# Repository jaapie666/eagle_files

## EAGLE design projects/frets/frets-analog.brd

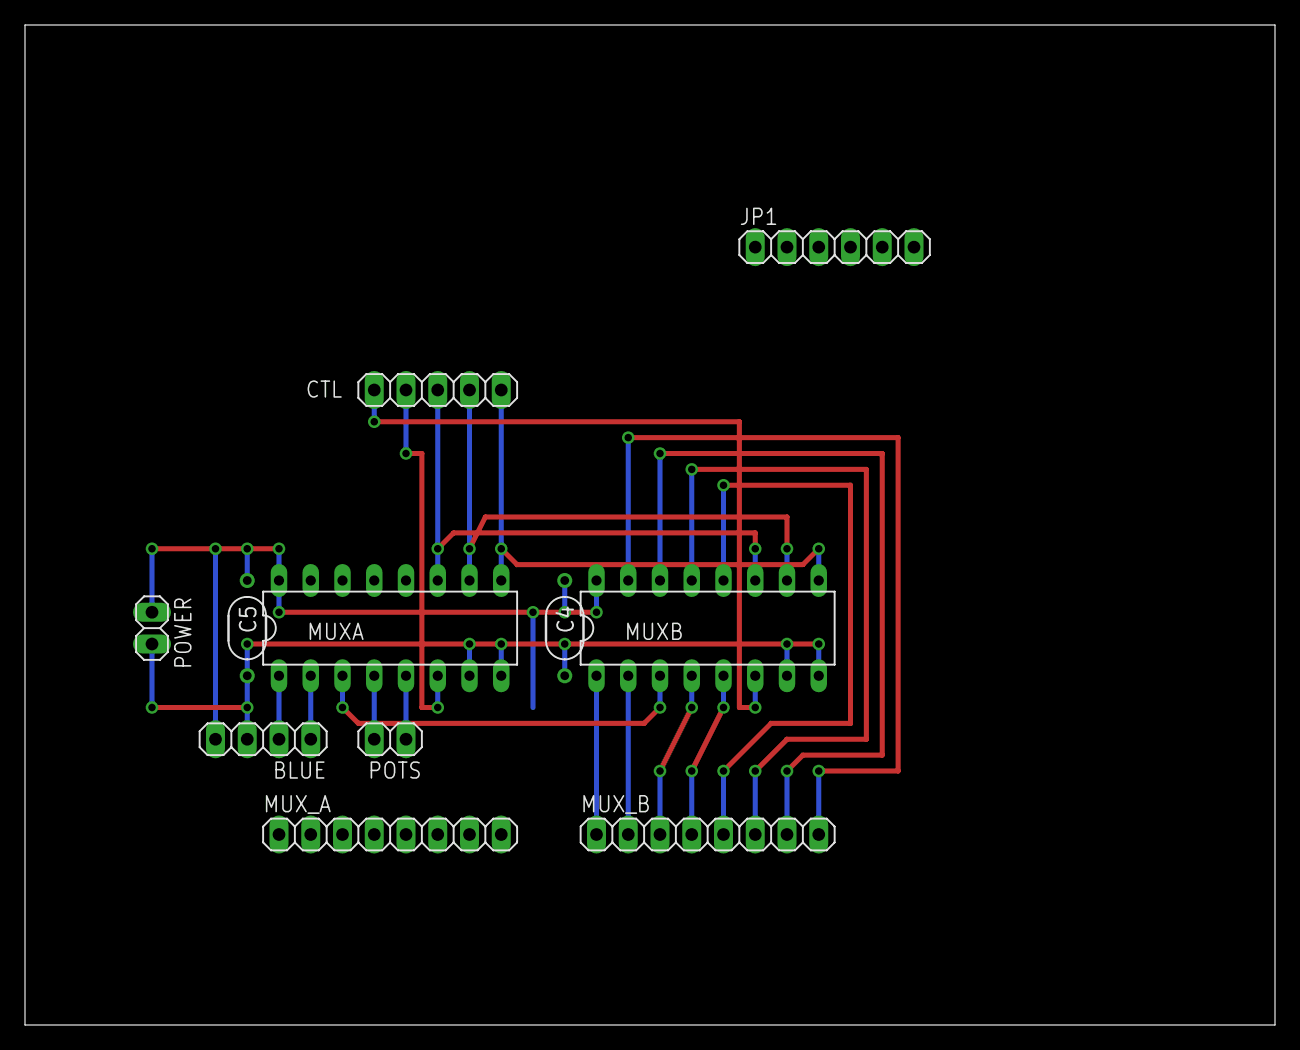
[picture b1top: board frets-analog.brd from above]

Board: 2 copper layers, 100.0 x 80.0 mm, 11 parts (0 on the bottom side), 20 nets.

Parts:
BLUE: 1X04
C4, C5: 100n; 050X030_050_3
CTL: 1X05
JP1: 1X06
MUXA: 4051N; DIL16
MUXB: 4051N; DIL16
MUX_A: 1X08
MUX_B: 1X08
POTS: 1X02
POWER: 1X02

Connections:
GND: BLUE.3, C4.2, C5.2, MUXA.7, MUXA.8, MUXB.7, MUXB.8, POWER.2
INH_A: CTL.4, MUXA.6
INH_B: CTL.5, MUXB.6
JOY_X: BLUE.1, MUXA.2
JOY_Y: BLUE.2, MUXA.1
MX_A: CTL.3, MUXA.11, MUXB.11
MX_B: CTL.2, MUXA.10, MUXB.10
MX_C: CTL.1, MUXA.9, MUXB.9
unnamed: JP1.1, MUXA.3, MUXB.3
unnamed: MUXB.1, MUX_B.1
unnamed: MUXB.2, MUX_B.2
unnamed: MUXB.4, MUX_B.3
unnamed: MUXB.5, MUX_B.4
unnamed: MUXB.12, MUX_B.5
unnamed: MUXB.13, MUX_B.6
unnamed: MUXB.14, MUX_B.7
unnamed: MUXB.15, MUX_B.8
POT_A: MUXA.5, POTS.1
POT_B: MUXA.4, POTS.2
VA: BLUE.4, C4.1, C5.1, MUXA.16, MUXB.16, POWER.1

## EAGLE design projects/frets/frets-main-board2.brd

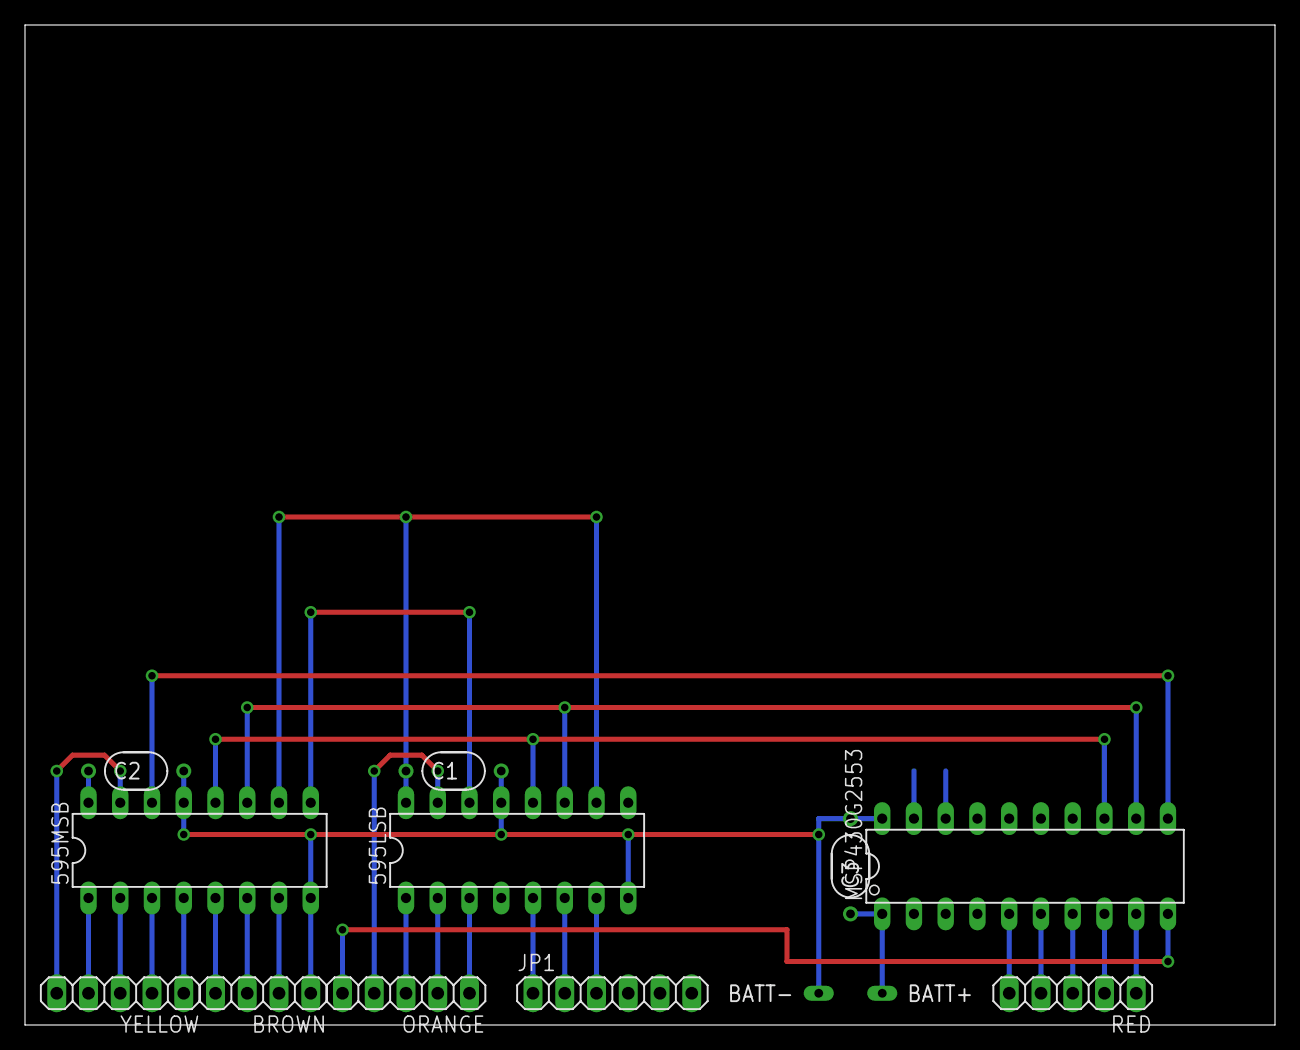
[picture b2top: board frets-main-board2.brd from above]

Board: 2 copper layers, 100.0 x 80.0 mm, 13 parts (0 on the bottom side), 30 nets.

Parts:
595LSB, 595MSB: 74LS595N; DIL16
BATT+: LONG
BATT-: LONG
BROWN: 1X04
C1, C2, C3: 100n; 050X030_050_3
JP1: 1X06
MSP430G2553: G2XX3---N20; N20
ORANGE: 1X05
RED: 1X05
YELLOW: 1X05

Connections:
A_IN: JP1.6, MSP430G2553.2
D0: MSP430G2553.5, RED.5
D1: MSP430G2553.6, RED.4
D2: MSP430G2553.7, RED.3
D3: MSP430G2553.8, RED.2
D4: MSP430G2553.9, RED.1
D5: MSP430G2553.10, ORANGE.5
GND: 595LSB.8, 595LSB.13, 595MSB.8, 595MSB.13, BATT-.1, BROWN.1, C1.2, C2.2, C3.2, MSP430G2553.20
INH_A: JP1.4, MSP430G2553.18
INH_B: JP1.5, MSP430G2553.19
MX_A: 595LSB.5, JP1.1
MX_B: 595LSB.6, JP1.2
MX_C: 595LSB.7, JP1.3
unnamed: 595LSB.14, 595MSB.9
RCK: 595LSB.12, 595MSB.12, MSP430G2553.13
SCK: 595LSB.11, 595MSB.11, MSP430G2553.12
SER: 595MSB.14, MSP430G2553.11
SR4: 595LSB.3, ORANGE.1
SR5: 595LSB.2, ORANGE.2
SR6: 595LSB.1, ORANGE.3
SR7: 595LSB.15, ORANGE.4
SR8: 595MSB.7, BROWN.2
SR9: 595MSB.6, BROWN.3
SR10: 595MSB.5, BROWN.4
SR11: 595MSB.4, YELLOW.1
SR12: 595MSB.3, YELLOW.2
SR13: 595MSB.2, YELLOW.3
SR14: 595MSB.1, YELLOW.4
SR15: 595MSB.15, YELLOW.5
VA: 595LSB.10, 595LSB.16, 595MSB.10, 595MSB.16, BATT+.1, C1.1, C2.1, C3.1, MSP430G2553.1

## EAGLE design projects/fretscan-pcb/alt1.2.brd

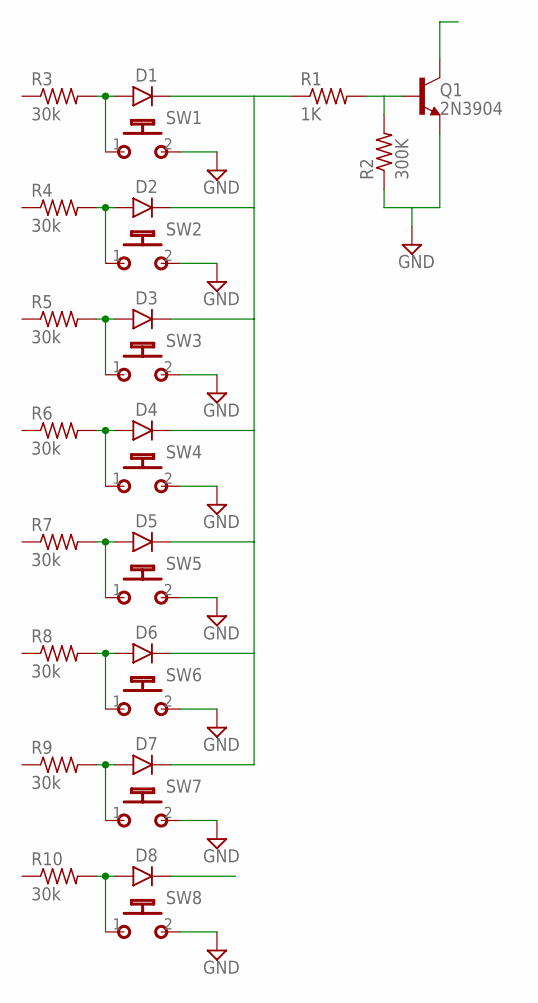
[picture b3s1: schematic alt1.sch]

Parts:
D1, D2, D3, D4, D5, D6, D7, D8: 1N4148-3; DO35-3
Q1: 2N3904; TO92-
R1: 1K; R0207/3
R2: 300K; R0207/3
R3, R4, R5, R6, R7, R8, R9, R10: 30k; R0207/3
SW1, SW2, SW3, SW4, SW5, SW6, SW7, SW8: MOMENTARYSPST1; SPST

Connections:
GND: Q1.3 (E), R2.1, SW1.2 (S), SW2.2 (S), SW3.2 (S), SW4.2 (S), SW5.2 (S), SW6.2 (S), SW7.2 (S), SW8.2 (S)
unnamed: Q1.2 (B), R1.2, R2.2
unnamed: D2.A, R4.2, SW2.1
unnamed: D1.A, R3.2, SW1.1
unnamed: D3.A, R5.2, SW3.1
unnamed: D4.A, R6.2, SW4.1
unnamed: D5.A, R7.2, SW5.1
unnamed: D6.A, R8.2, SW6.1
unnamed: D1.C, D2.C, D3.C, D4.C, D5.C, D6.C, D7.C, R1.1
unnamed: D7.A, R9.2, SW7.1
unnamed: D8.A, R10.2, SW8.1

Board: 2 copper layers, 27 parts (0 on the bottom side), 11 nets, no tracks yet.

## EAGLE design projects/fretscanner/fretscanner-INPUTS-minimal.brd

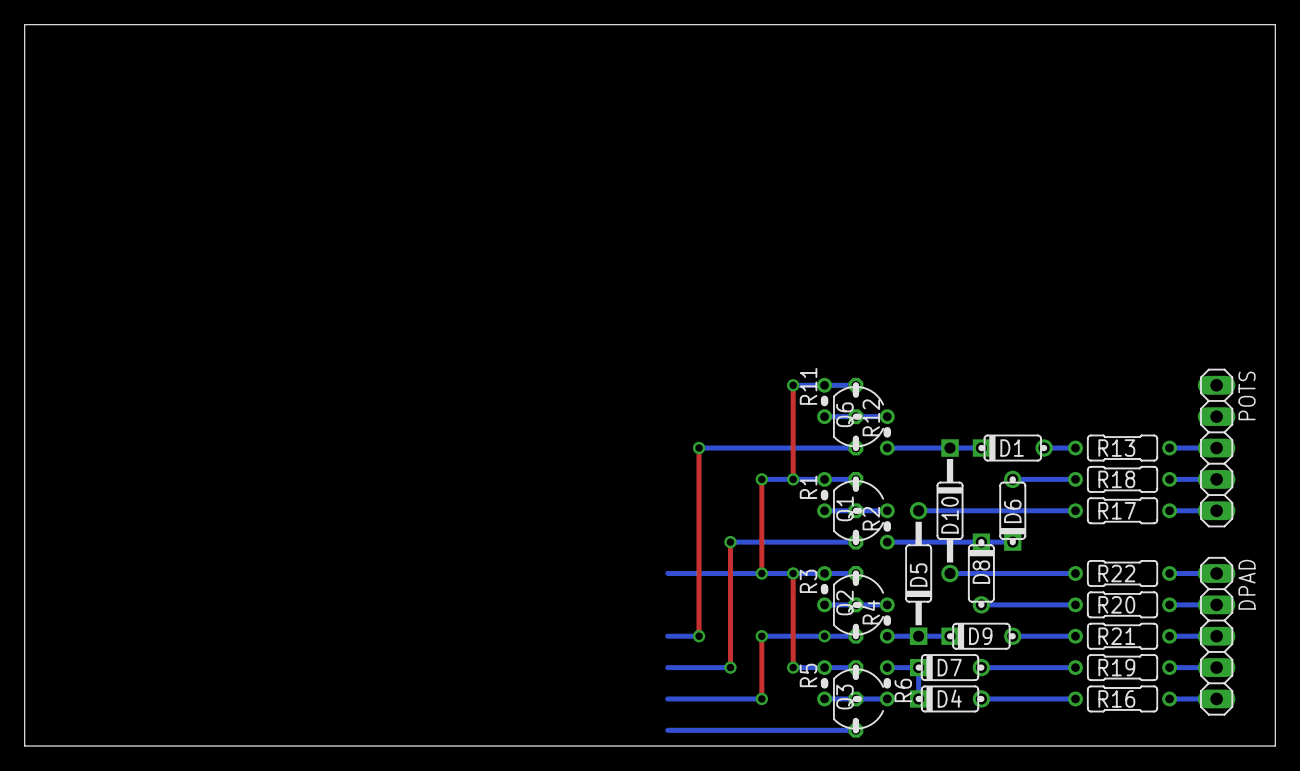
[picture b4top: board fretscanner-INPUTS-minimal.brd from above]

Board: 2 copper layers, 101.3 x 58.4 mm, 30 parts (0 on the bottom side), 25 nets.

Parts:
D1, D4, D6, D7, D8, D9: 1N4148-2; DO35-2
D5, D10: 1N4148-4; DO35-4
DPAD: 1X05
POTS: 1X05
Q1, Q2, Q3, Q6: 2N3904; TO92-
R1, R3, R5, R11: 300k; R0207/1V
R2, R4, R6, R12: 1k; R0207/1V
R13, R16, R17, R18, R19, R20, R21, R22: 30k; R0207/3

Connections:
BACK: POTS.4, R18.1
D_DOWN: DPAD.1, R22.1
D_LEFT: DPAD.2, R20.1
D_RIGHT: DPAD.3, R21.1
D_UP: DPAD.4, R19.1
GND: Q1.3, Q2.3, Q3.3, Q6.3, R1.2, R3.2, R5.2, R11.2
unnamed: Q2.2, R3.1, R4.2
unnamed: D5.C, D9.C, R4.1
unnamed: Q3.2, R5.1, R6.2
unnamed: Q1.2, R1.1, R2.2
unnamed: D6.C, D8.C, R2.1
unnamed: D4.A, R16.2
unnamed: D5.A, R17.2
unnamed: D4.C, D7.C, R6.1
unnamed: D6.A, R18.2
unnamed: D1.A, R13.2
unnamed: Q6.2, R11.1, R12.2
unnamed: D1.C, D10.C, R12.1
unnamed: D7.A, R19.2
unnamed: D8.A, R20.2
unnamed: D9.A, R21.2
unnamed: D10.A, R22.2
SIDE_B: POTS.5, R17.1
START: POTS.3, R13.1
X_BUTTON: DPAD.5, R16.1

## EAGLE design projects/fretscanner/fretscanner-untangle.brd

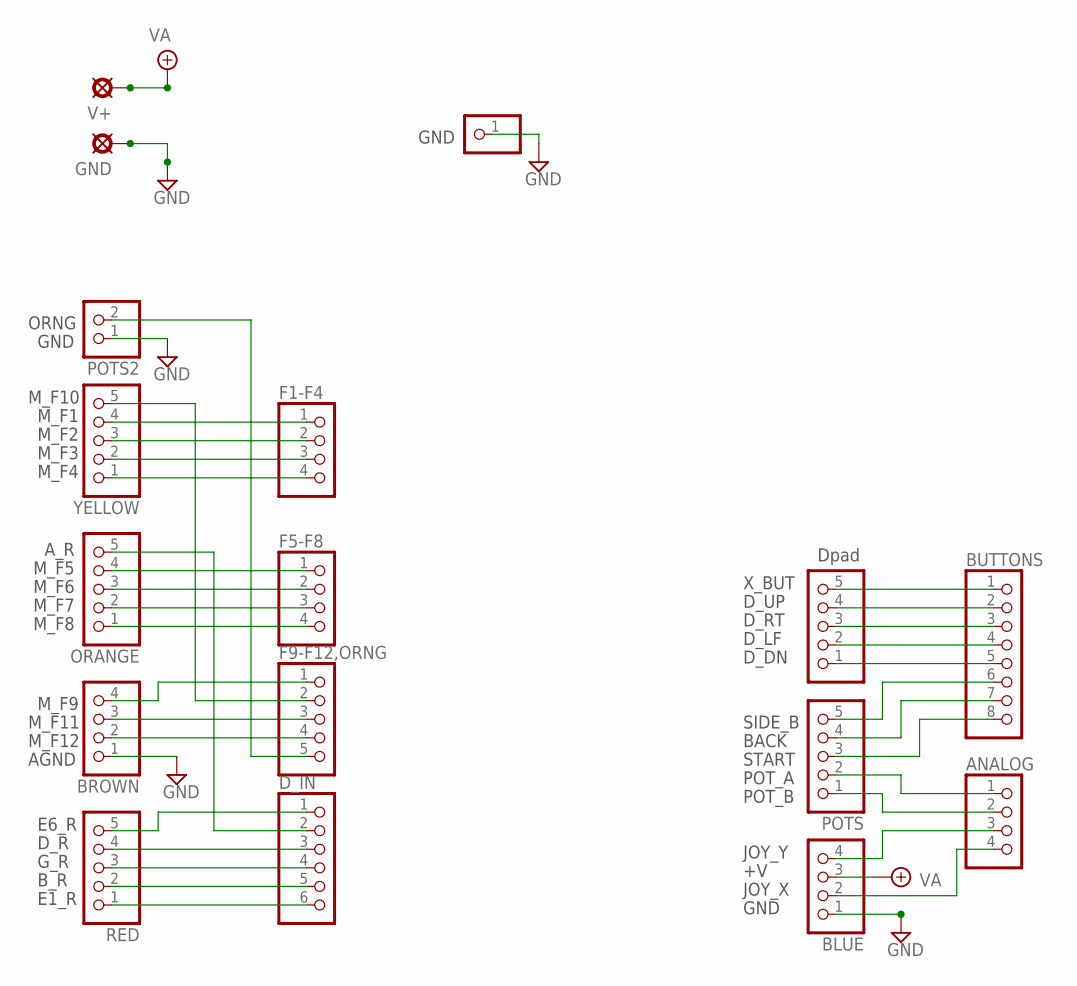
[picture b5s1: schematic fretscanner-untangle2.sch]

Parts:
ANALOG: PINHD-1X4; 1X04
BLUE: PINHD-1X4; 1X04
BROWN: PINHD-1X4; 1X04
BUTTONS: PINHD-1X8; 1X08
DPAD: PINHD-1X5; 1X05
DPAD2: PINHD-1X1; 1X01
D_IN: PINHD-1X6; 1X06
F1-F4, F5-F8: PINHD-1X4; 1X04
F9-F12,ORNG: PINHD-1X5; 1X05
GND: PADL; LONG
ORANGE: PINHD-1X5; 1X05
POTS: PINHD-1X5; 1X05
POTS2: PINHD-1X2; 1X02
RED: PINHD-1X5; 1X05
V+: PADL; LONG
YELLOW: PINHD-1X5; 1X05

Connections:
BACK: BUTTONS.7, POTS.4
D0: D_IN.1, RED.5
GND: BLUE.1, BROWN.1, DPAD2.1, GND.1, POTS2.1
JOY_X: ANALOG.4, BLUE.2
JOY_Y: ANALOG.3, BLUE.4
unnamed: F1-F4.1, YELLOW.4
unnamed: F1-F4.2, YELLOW.3
unnamed: F1-F4.3, YELLOW.2
unnamed: F1-F4.4, YELLOW.1
unnamed: F5-F8.1, ORANGE.4
unnamed: F5-F8.2, ORANGE.3
unnamed: F5-F8.3, ORANGE.2
unnamed: F5-F8.4, ORANGE.1
unnamed: BROWN.4, F9-F12,ORNG.1
unnamed: F9-F12,ORNG.2, YELLOW.5
unnamed: D_IN.3, RED.4
unnamed: D_IN.4, RED.3
unnamed: D_IN.2, ORANGE.5
unnamed: BROWN.3, F9-F12,ORNG.3
unnamed: BROWN.2, F9-F12,ORNG.4
unnamed: F9-F12,ORNG.5, POTS2.2
unnamed: D_IN.5, RED.2
unnamed: D_IN.6, RED.1
unnamed: BUTTONS.1, DPAD.5
unnamed: BUTTONS.2, DPAD.4
unnamed: BUTTONS.3, DPAD.3
unnamed: BUTTONS.4, DPAD.2
unnamed: BUTTONS.5, DPAD.1
POT_A: ANALOG.1, POTS.2
POT_B: ANALOG.2, POTS.1
SIDE_B: BUTTONS.6, POTS.5
START: BUTTONS.8, POTS.3
VA: BLUE.3, V+.1

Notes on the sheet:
Dpad
A_R
M_F5
M_F6
M_F7
M_F8
M_F10
M_F1
M_F2
M_F3
M_F4
M_F9
M_F11
M_F12
AGND
E6_R
D_R
G_R
B_R
E1_R
X_BUT
D_UP
D_RT
D_LF
D_DN
GND
SIDE_B
BACK
START
POT_A
POT_B
ORNG
JOY_X
JOY_Y

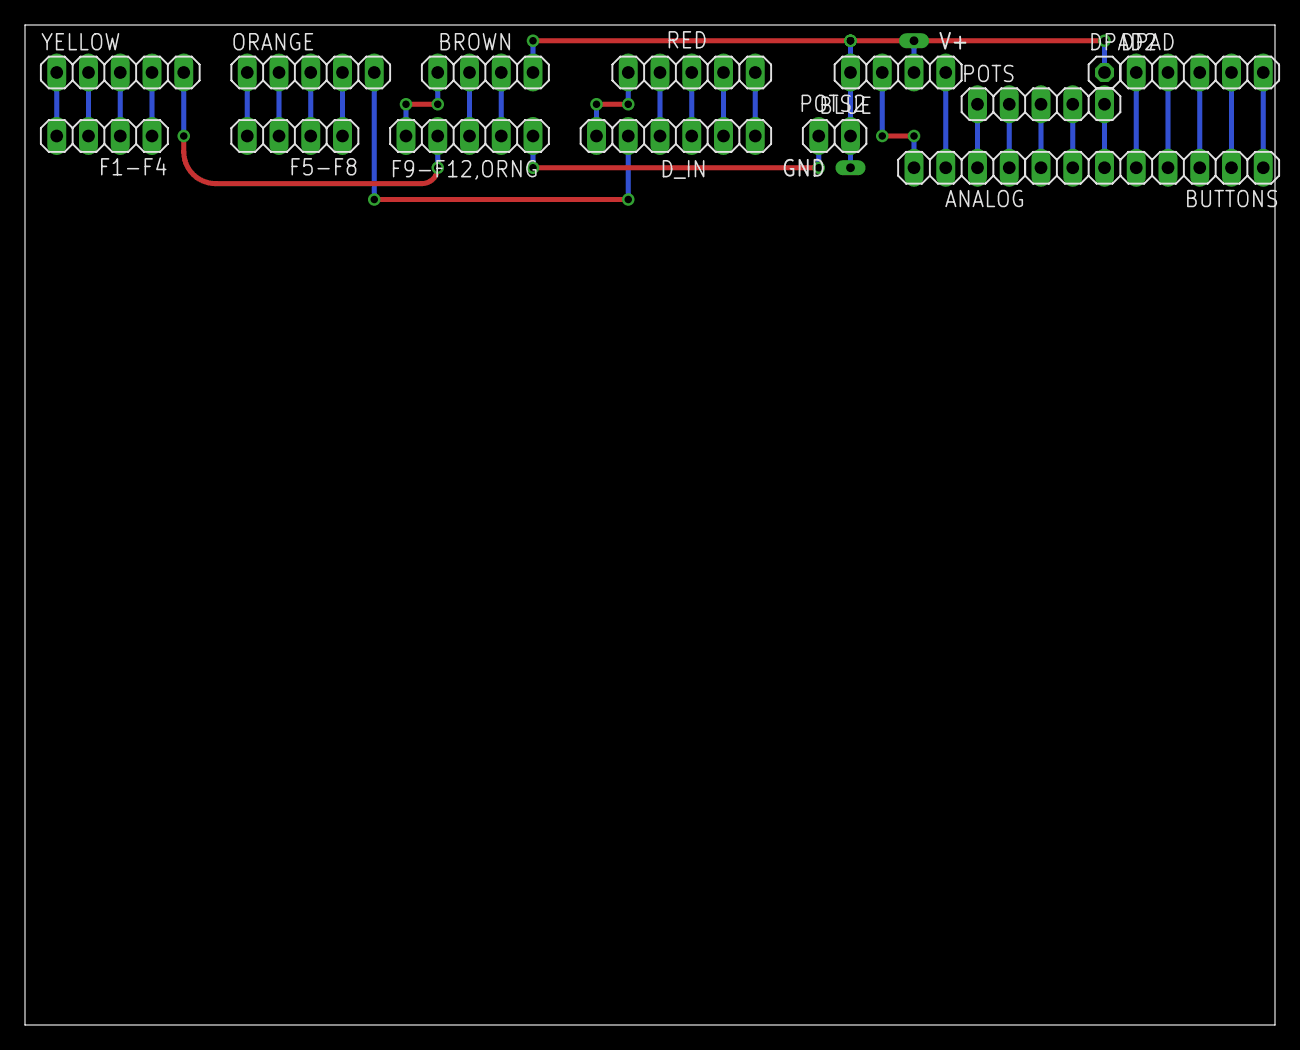
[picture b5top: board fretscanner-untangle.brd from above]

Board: 2 copper layers, 100.0 x 80.0 mm, 17 parts (0 on the bottom side), 33 nets.

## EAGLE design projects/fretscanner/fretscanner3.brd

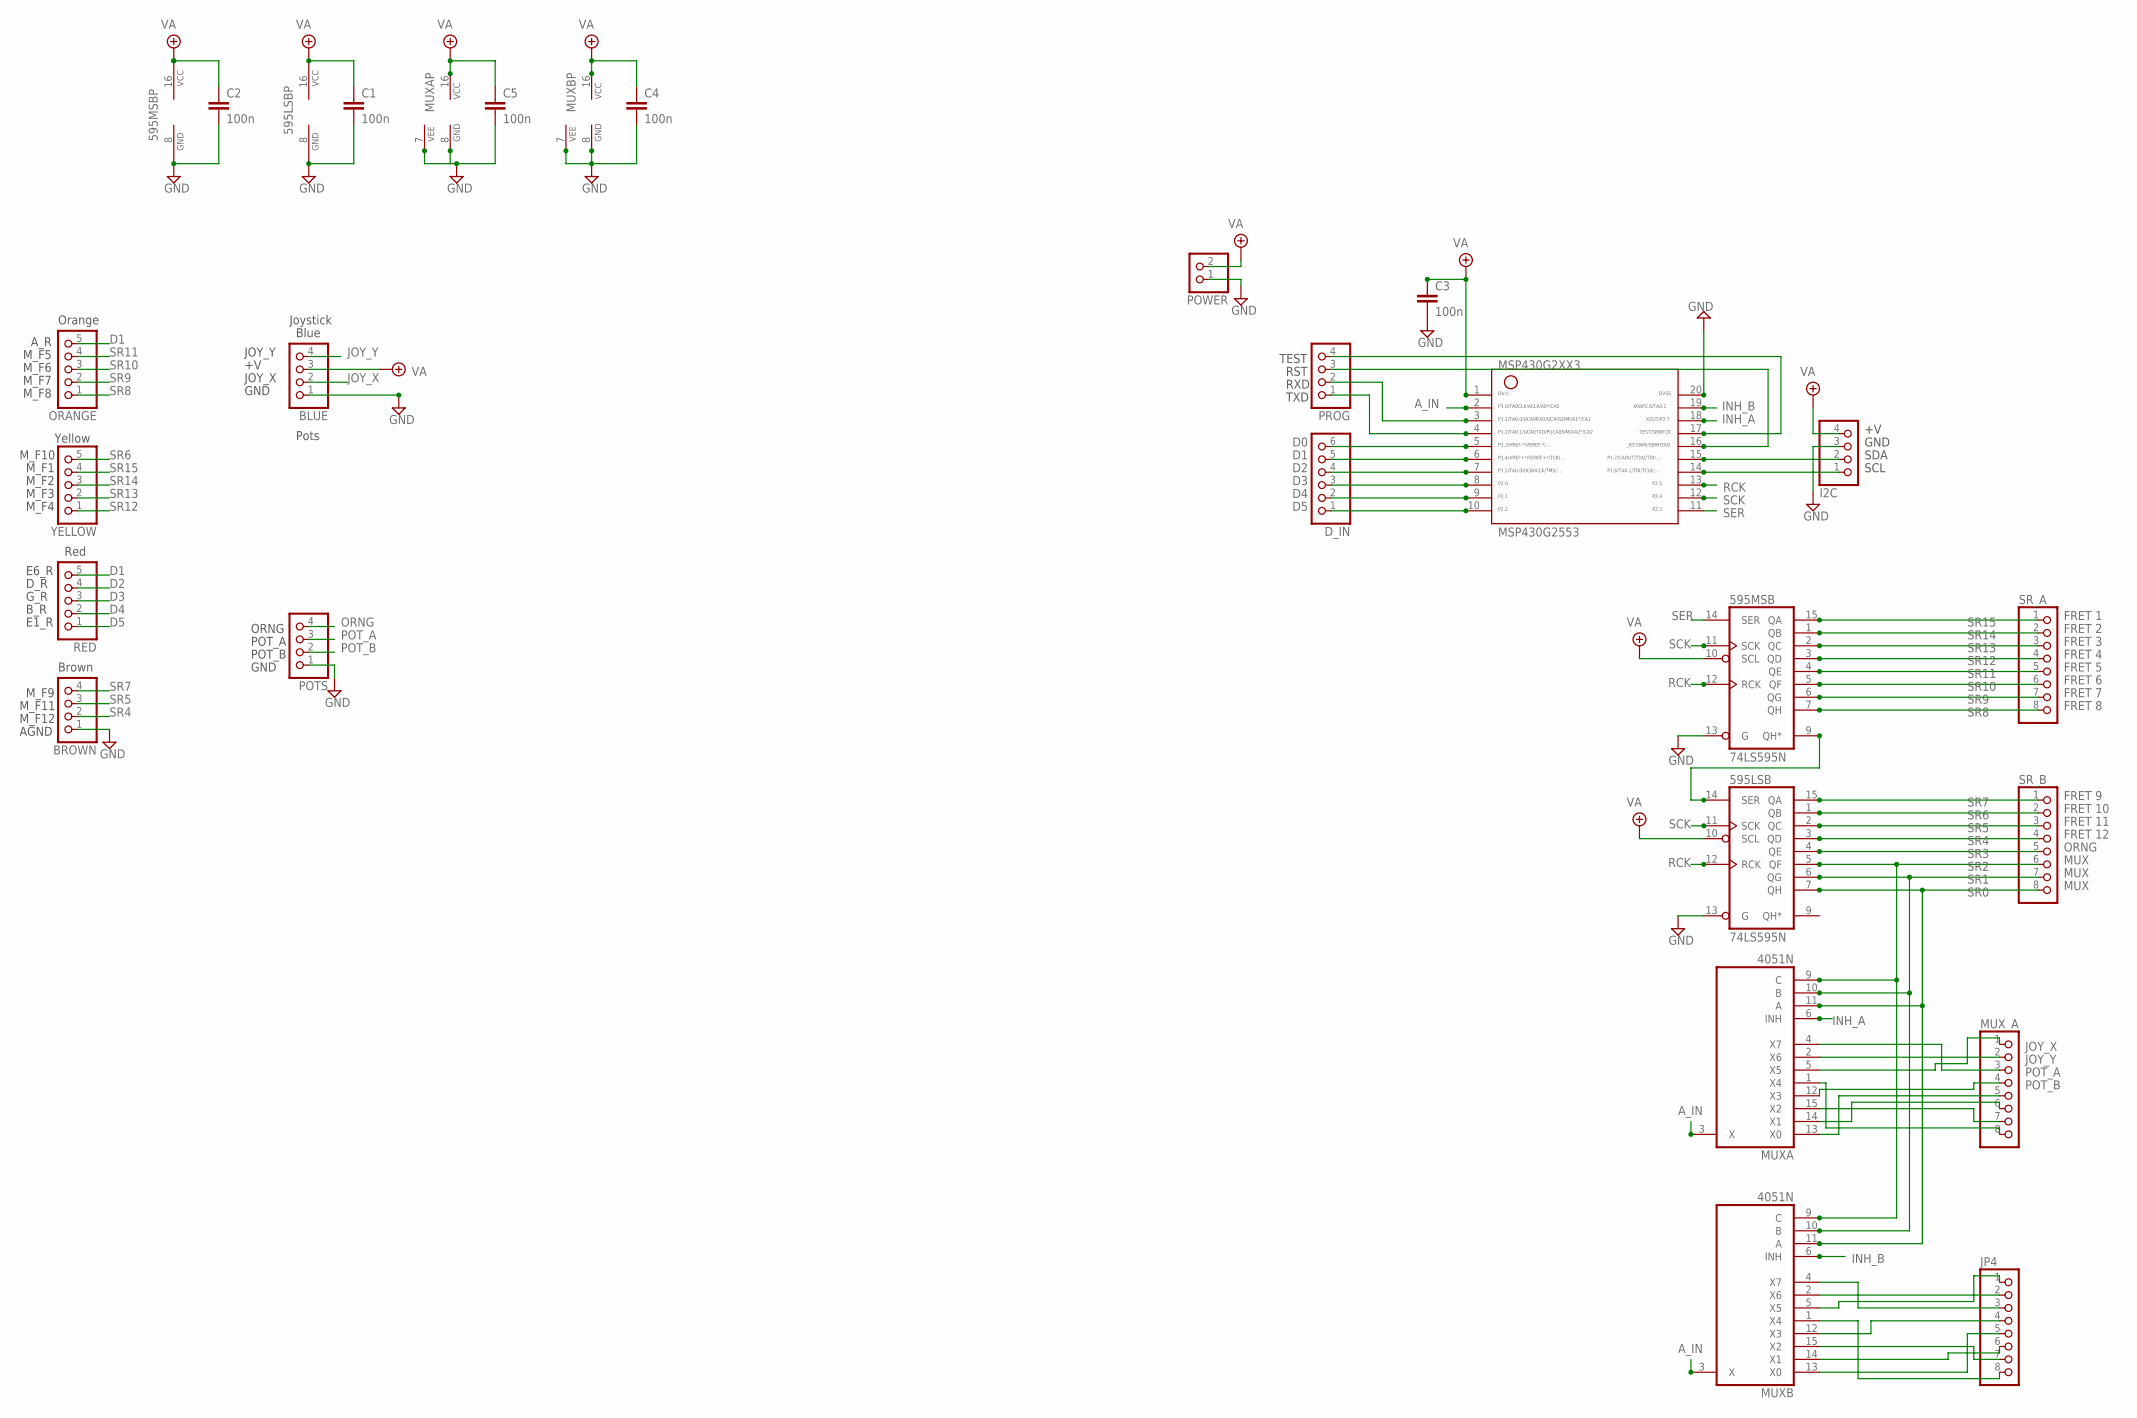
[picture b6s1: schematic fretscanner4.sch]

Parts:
595LSB, 595MSB: 74LS595N; DIL16
BLUE: PINHD-1X4; 1X04
BROWN: PINHD-1X4; 1X04
C1, C2, C3, C4, C5: 100n; 050X030_050_3
D_IN: PINHD-1X6; 1X06
I2C: PINHD-1X4; 1X04
JP4: PINHD-1X8; 1X08
MSP430G2553: G2XX3---N20; N20
MUXA: 4051N; DIL16
MUXB: 4051N; DIL16
MUX_A: PINHD-1X8; 1X08
ORANGE: PINHD-1X5; 1X05
POTS: PINHD-1X4; 1X04
POWER: PINHD-1X2; 1X02
PROG: PINHD-1X4; 1X04
RED: PINHD-1X5; 1X05
SR_A: PINHD-1X8; 1X08
SR_B: PINHD-1X8; 1X08
YELLOW: PINHD-1X5; 1X05

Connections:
A_IN: MSP430G2553.2, MUXA.3 (X), MUXB.3 (X)
D0: D_IN.6, MSP430G2553.5
D1: D_IN.5, MSP430G2553.6, ORANGE.5, RED.5
D2: D_IN.4, MSP430G2553.7, RED.4
D3: D_IN.3, MSP430G2553.8, RED.3
D4: D_IN.2, MSP430G2553.9, RED.2
D5: D_IN.1, MSP430G2553.10, RED.1
GND: 595LSB.8 (GND), 595LSB.13 (G), 595MSB.8 (GND), 595MSB.13 (G), BLUE.1, BROWN.1, C1.2, C2.2, C3.2, C4.2, C5.2, I2C.3, MSP430G2553.20, MUXA.7 (VEE), MUXA.8 (GND), MUXB.7 (VEE), MUXB.8 (GND), POTS.1, POWER.1
INH_A: MSP430G2553.18, MUXA.6 (INH)
INH_B: MSP430G2553.19, MUXB.6 (INH)
JOY_X: BLUE.2, MUXA.5 (X5), MUX_A.1
JOY_Y: BLUE.4, MUXA.2 (X6), MUX_A.2
unnamed: 595LSB.14 (SER), 595MSB.9 (QH*)
unnamed: MUXA.15 (X2), MUX_A.7
unnamed: MUXA.14 (X1), MUX_A.6
unnamed: MUXA.13 (X0), MUX_A.5
unnamed: JP4.3, MUXB.4 (X7)
unnamed: JP4.2, MUXB.2 (X6)
unnamed: JP4.1, MUXB.5 (X5)
unnamed: JP4.8, MUXB.1 (X4)
unnamed: JP4.4, MUXB.12 (X3)
unnamed: JP4.7, MUXB.15 (X2)
unnamed: MUXA.1 (X4), MUX_A.8
unnamed: JP4.6, MUXB.14 (X1)
unnamed: JP4.5, MUXB.13 (X0)
ORNG: POTS.4
POT_A: MUXA.4 (X7), MUX_A.3, POTS.3
POT_B: MUXA.12 (X3), MUX_A.4, POTS.2
RCK: 595LSB.12 (RCK), 595MSB.12 (RCK), MSP430G2553.13
RXD: MSP430G2553.3, PROG.2
SCK: 595LSB.11 (SCK), 595MSB.11 (SCK), MSP430G2553.12
SCL: I2C.1, MSP430G2553.14
SDA: I2C.2, MSP430G2553.15
SER: 595MSB.14 (SER), MSP430G2553.11
SR0: 595LSB.7 (QH), MUXA.11 (A), MUXB.11 (A), SR_B.8
SR1: 595LSB.6 (QG), MUXA.10 (B), MUXB.10 (B), SR_B.7
SR2: 595LSB.5 (QF), MUXA.9 (C), MUXB.9 (C), SR_B.6
SR3: 595LSB.4 (QE), SR_B.5
SR4: 595LSB.3 (QD), BROWN.2, SR_B.4
SR5: 595LSB.2 (QC), BROWN.3, SR_B.3
SR6: 595LSB.1 (QB), SR_B.2, YELLOW.5
SR7: 595LSB.15 (QA), BROWN.4, SR_B.1
SR8: 595MSB.7 (QH), ORANGE.1, SR_A.8
SR9: 595MSB.6 (QG), ORANGE.2, SR_A.7
SR10: 595MSB.5 (QF), ORANGE.3, SR_A.6
SR11: 595MSB.4 (QE), ORANGE.4, SR_A.5
SR12: 595MSB.3 (QD), SR_A.4, YELLOW.1
SR13: 595MSB.2 (QC), SR_A.3, YELLOW.2
SR14: 595MSB.1 (QB), SR_A.2, YELLOW.3
SR15: 595MSB.15 (QA), SR_A.1, YELLOW.4
TEST: MSP430G2553.17, PROG.4
TXD: MSP430G2553.4, PROG.1
VA: 595LSB.10 (SCL), 595LSB.16 (VCC), 595MSB.10 (SCL), 595MSB.16 (VCC), BLUE.3, C1.1, C2.1, C3.1, C4.1, C5.1, I2C.4, MSP430G2553.1, MUXA.16 (VCC), MUXB.16 (VCC), POWER.2
_RST: MSP430G2553.16, PROG.3

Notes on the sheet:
Yellow
Orange
Red
Brown
Joystick
Pots
Blue
A_R
M_F5
M_F6
M_F7
M_F8
M_F10
M_F1
M_F2
M_F3
M_F4
M_F9
M_F11
M_F12
AGND
E6_R
D_R
G_R
B_R
E1_R
POT_A
POT_B
ORNG
GND
JOY_X
JOY_Y
RXD
TXD
TEST
RST
SDA
SCL
FRET 1
FRET 2

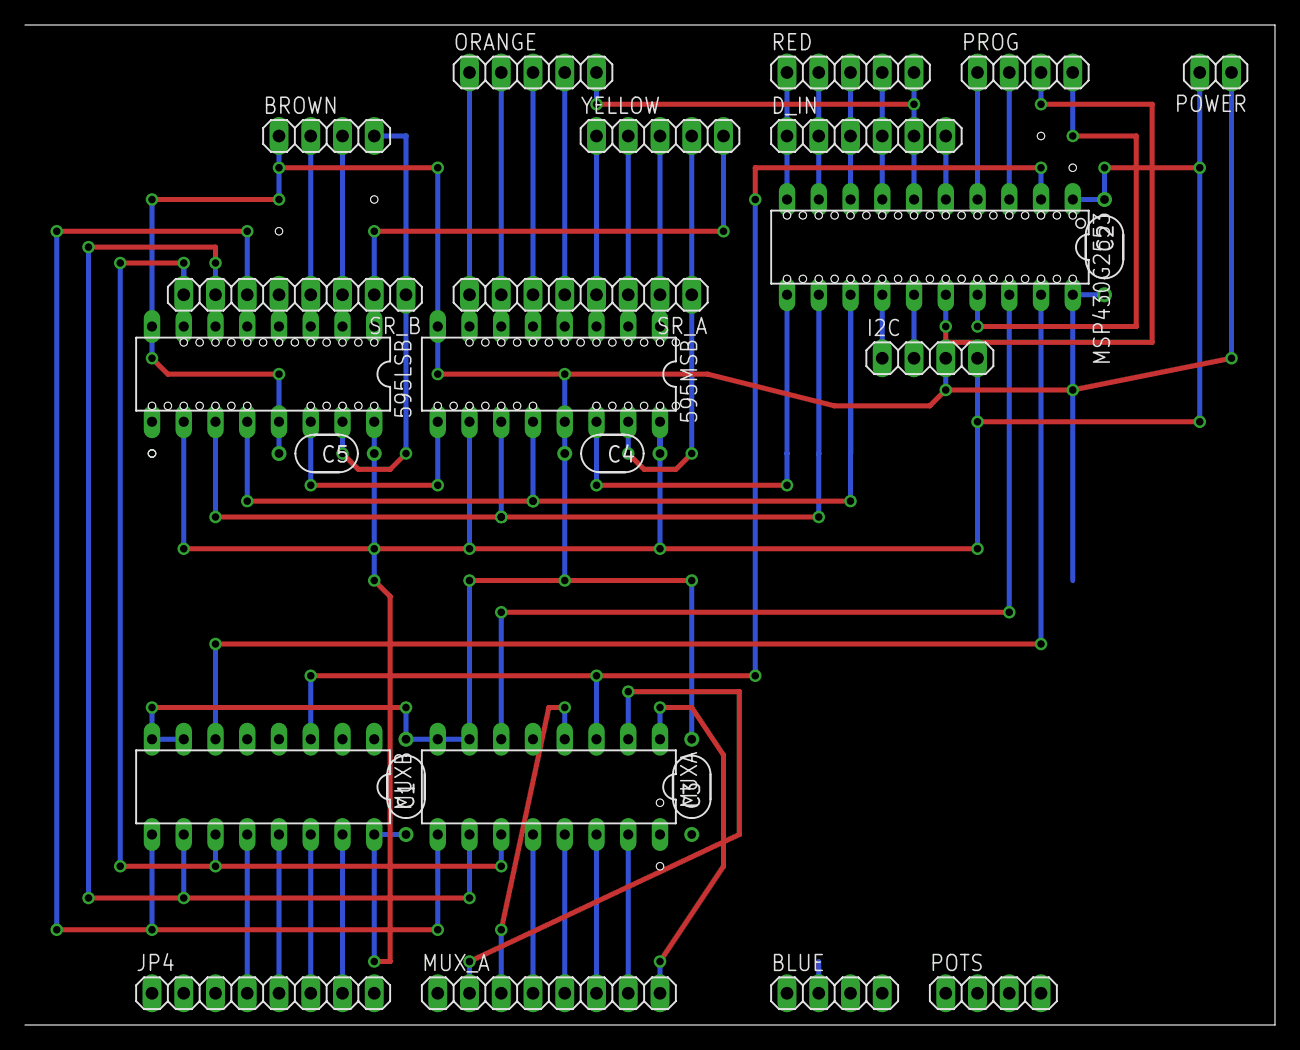
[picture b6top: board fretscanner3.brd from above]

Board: 2 copper layers, 100.0 x 80.0 mm, 24 parts (0 on the bottom side), 53 nets.
